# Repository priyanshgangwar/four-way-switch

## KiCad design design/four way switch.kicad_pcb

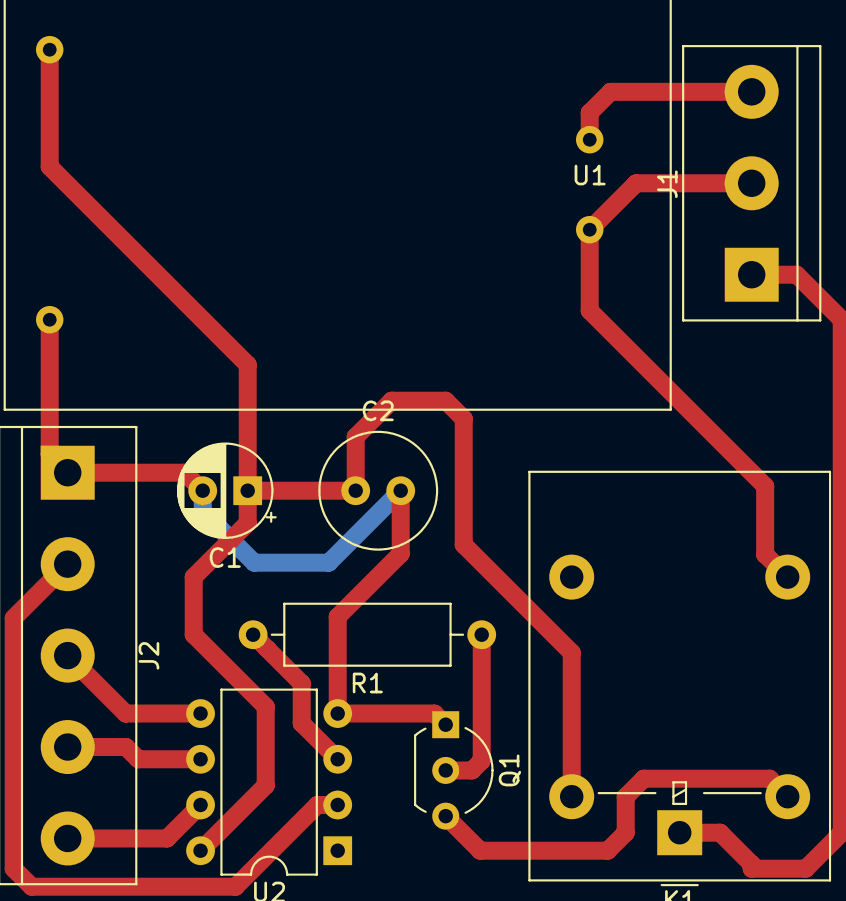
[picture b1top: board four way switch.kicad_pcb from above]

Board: 2 copper layers, 9 parts (0 on the bottom side), 12 nets.

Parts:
C1: CP_Small; CP_Radial_D5.0mm_P2.50mm
C2: C_Small; C_Radial_D6.3mm_H5.0mm_P2.50mm
J1: Screw_Terminal_01x03; TerminalBlock_bornier-3_P5.08mm
J2: Screw_Terminal_01x05; TerminalBlock_bornier-5_P5.08mm
K1: G5LE-1; Relay_SPDT_Omron-G5LE-1
Q1: 2N3904; TO-92L_Inline_Wide
R1: R; R_Axial_DIN0309_L9.0mm_D3.2mm_P12.70mm_Horizontal
U1: AC_80-230V--DC_5V-700mA
U2: ATtiny13A-PU; DIP-8_W7.62mm

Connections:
+5V: C1.1, C2.1, K1.5, U1.4, U2.8
Earth: C1.2, C2.2, J2.1, Q1.1, U1.3, U2.4
LINE: J1.2, K1.3, U1.1
NEUTRAL: J1.3, U1.2
unnamed: K1.2, Q1.3
unnamed: Q1.2, R1.1
unnamed: R1.2, U2.3
OUTPUT: J1.1, K1.1
SWITCH-A: J2.3, U2.5
SWITCH-B: J2.4, U2.6
SWITCH-C: J2.5, U2.7
SWITCH-D: J2.2, U2.2
